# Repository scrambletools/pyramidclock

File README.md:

# pryamidclock
Pyramid Clock design files

This repository contains the DXF for the clock face as well as the libraries and project files for the PCB design in Kicad. The BOM is not yet provided, but you can get some part numbers from the Kicad project. These files are subject to MIT license so you can use it freely for personal or commercial use.

Visit www.pyramidclock.com for more info.

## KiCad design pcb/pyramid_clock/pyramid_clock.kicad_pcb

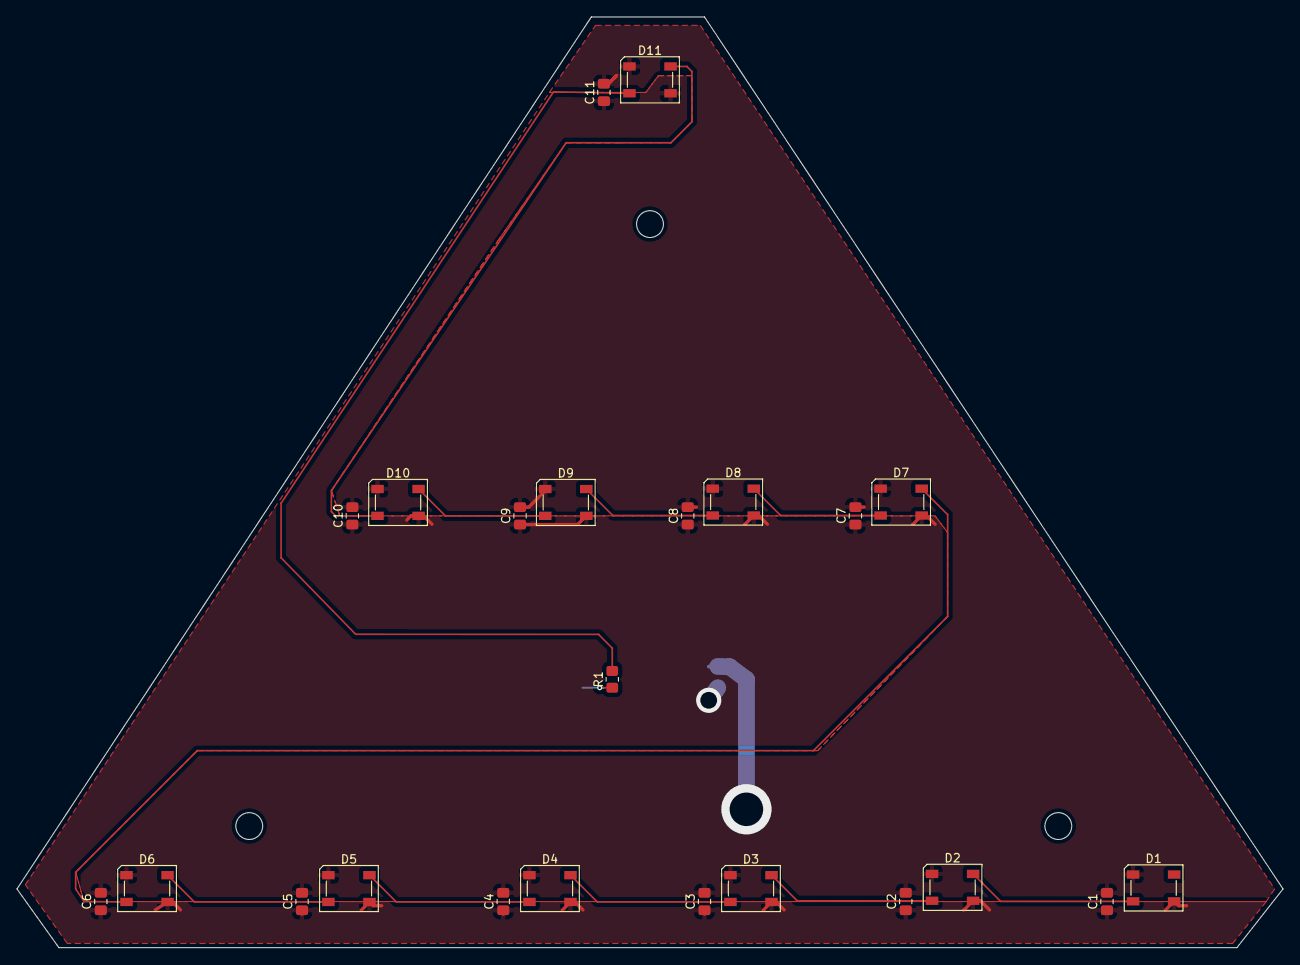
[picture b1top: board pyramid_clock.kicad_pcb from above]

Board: 2 copper layers, 151.0 x 111.0 mm, 24 parts (1 on the bottom side), 13 nets.

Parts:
C1, C2, C3, C4, C5, C6, C7, C8, C9, C10, C11: 100nF; C_0805_2012Metric_Pad1.18x1.45mm_HandSolder
D1, D2, D3, D4, D5, D6, D7, D8, D9, D10, D11: SK6812; LED_SK6812_PLCC4_5.0x5.0mm_P3.2mm
R1: 330R; R_0805_2012Metric_Pad1.20x1.40mm_HandSolder
U1: SEEEDUINO-XIAO-ESP32C3; MOUDLE14P-SMD-2.54-21X17.8MM

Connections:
unnamed: D1.2 (DIN), D2.4 (DOUT)
unnamed: C1.1, C2.1, C3.1, C4.1, C5.1, C6.1, C7.1, C8.1, C9.1, C10.1, C11.1, D1.3 (VDD), D2.3 (VDD), D3.3 (VDD), D4.3 (VDD), D5.3 (VDD), D6.3 (VDD), D7.3 (VDD), D8.3 (VDD), D9.3 (VDD), D10.3 (VDD), D11.3 (VDD), U1.14 (5V)
unnamed: C1.2, C2.2, C3.2, C4.2, C5.2, C6.2, C7.2, C8.2, C9.2, C10.2, C11.2, D1.1 (VSS), D2.1 (VSS), D3.1 (VSS), D4.1 (VSS), D5.1 (VSS), D6.1 (VSS), D7.1 (VSS), D8.1 (VSS), D9.1 (VSS), D10.1 (VSS), D11.1 (VSS), U1.13 (GND)
unnamed: D2.2 (DIN), D3.4 (DOUT)
unnamed: D3.2 (DIN), D4.4 (DOUT)
unnamed: D4.2 (DIN), D5.4 (DOUT)
unnamed: D5.2 (DIN), D6.4 (DOUT)
unnamed: D6.2 (DIN), D7.4 (DOUT)
unnamed: D7.2 (DIN), D8.4 (DOUT)
unnamed: D8.2 (DIN), D9.4 (DOUT)
unnamed: D10.2 (DIN), D11.4 (DOUT)
unnamed: D9.2 (DIN), D10.4 (DOUT)
unnamed: D11.2 (DIN), R1.2

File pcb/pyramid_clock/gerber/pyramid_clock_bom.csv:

"Id";"Designator";"Footprint";"Quantity";"Designation";"Supplier and ref";
1;"D8,D4,D5,D10,D3,D11,D1,D7,D2,D9,D6";"LED_SK6812_PLCC4_5.0x5.0mm_P3.2mm";11;"SK6812";;;
2;"C6,C4,C11,C9,C10,C3,C2,C1,C7,C8,C5";"C_0805_2012Metric_Pad1.18x1.45mm_HandSolder";11;"100nF";;;
3;"R1";"R_0805_2012Metric_Pad1.20x1.40mm_HandSolder";1;"330R";;;
4;"U1";"MOUDLE14P-SMD-2.54-21X17.8MM";1;"SEEEDUINO-XIAO-ESP32C3";;;

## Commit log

2025-11-20 updated design, saved gerber and bom
